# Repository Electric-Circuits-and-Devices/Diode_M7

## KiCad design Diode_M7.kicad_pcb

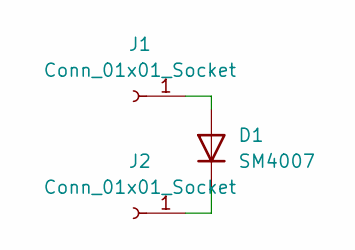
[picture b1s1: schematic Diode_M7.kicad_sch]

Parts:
D1: SM4007; D_SMA
J1, J2: Conn_01x01_Socket; MountingHole_2.5mm_Pad

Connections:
unnamed: D1.2 (A), J1.1
unnamed: D1.1 (K), J2.1

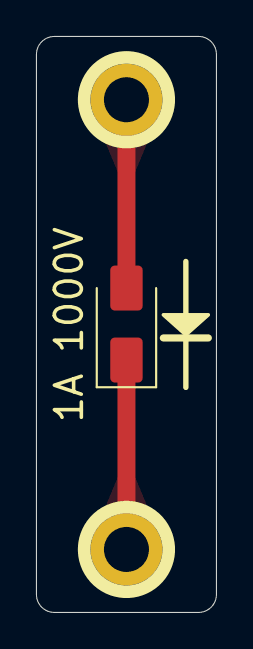
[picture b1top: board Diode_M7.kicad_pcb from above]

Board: 2 copper layers, 10.0 x 32.0 mm, 3 parts (0 on the bottom side), 2 nets.
